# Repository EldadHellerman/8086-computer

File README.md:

# 8086 computer

A single board 8086 based computer with a full keyboard and RGB LCD screen.
The project includes an assembler, and maybe in the future a c compiler.

It's a new version of my 8086 computer (the old one moved to repository "8086_OLD").
This one focuses mainly on PCB design.

Folders in this repository:
 - 8086 board - KiCad project folder. Schematics and PCB design.
 - assembler - Custom 8086 assembler.
 - coprocessor - Software for the coprocessor.
 - companion - Utility to communicate with the coprocessor.

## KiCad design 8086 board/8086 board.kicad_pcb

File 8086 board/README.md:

# 8086 board
This folder is a KiCad project folder.
It includes the 8086 PC schematics and PCB design.

## Board details

### General
- The 8086 itself.
- 128/256kB SRAM + 1024kB flash with bank select switch (only 512kB are addressable at a time, so flash is divided into two banks, meaning two complete programs can be stored at once, and selected from using the switch before boot).
- Logic for address latching (including OR gate with bus ALE).
- Expansion port allowing access to 8086 bus.
This may be used for future developments - perhapse an FPGA graphics card with HDMI output.
- LED indicators for: latched adderss, memory access (SRAM 1, SRAM 2, Flash is A19, MCU, and LCD).
- Reset button.
- USB-C port for power and communication with coprocessor.

### IO
- 320*240 or 480*320 RGB 40 pin LCD.
- 32 Push Buttons.  
They form a keyboard, with 'a'-'z', space, enter, backspace, CTRL, ALT, SHIFT.
- Logic to latch data from buttons.

### Co-Processor
- Mircocontroller used to control the 8086 (generating clock and reset signals), programming the memory and generating interrupts.
- Clock source: if I dont want to generate 33% duty cycle, than maybe a lower frequency 50% duty cycle instead.
  (make 66% of 8MHz the 50% of frequency - which is 6MHz).
- Maybe also act as peripherals (with or without interrupts): timers, UART, mouse (input from touch screen), SD card interface, etc...
- USB to UART convertor (CH340C).
- USB-C port for power and to connect to computer.
- UART connector (4p header pins or JST-XH).

## Address Space

### Segments and physical address

The 8086 uses 20-bit addressing (for 1MB total).  
The physical address is calculated from a 16-bit segment register and a 16-bit address register:

```
physical address = (segment << 4) + offset
```

For convenience, I will think of each segment as being only the 4 highest order bits (0x?000), and the memory as being comprised of 16 segments, each 64kB in size.
    
For in / out instructions, only 16-bits addressing is allowed (first segment only).

The 8086 boots to address 0xFFFF0, so there must be some memory there. That's why the flash is at the top of the memory map.  
Interrupt vector table is at 0x000 - 0x100. That's why the SRAM is at the bottom of the memory map.

<details>
<summary>Tables of memory and IO maps:</summary>

### Memory map

| Addresses             | Segments  | Size  | Description                       |
| --------------------- | --------- | ----- | --------------------------------- |
| 0x0_0000 - 0x2_0000   | 0 - 1     | 128kB | SRAM                              |
| 0x2_0000 - 0x4_0000   | 2 - 3     | 128kB | optional additional SRAM          |
| 0x4_0000 - 0x6_0000   | 4 - 5     | 128kB | MMIO - Microcontroller            |
| 0x6_0000 - 0x7_0000   | 6         | 64 kB | MMIO - RGB LCD - DATA             |
| 0x7_8000 - 0x8_0000   | 7         | 64 kB | MMIO - RGB LCD  - COMMAND         |
| 0x8_0000 - 0xF_FFFF   | 8 - 15    | 512kB | Flash                             |

### IO map

IO ports are 16-bit wide.

| Number    | Address         | Read description | Write description    |
| --------- | --------------- | ---------------- | -------------------- |
| 0         | 0x0000          | 16 Push buttons. | FREE                 |
| 1         | 0x0002          | 16 Push buttons. | FREE                 |
| 2 - 7     | 0x0004 - 0x000E | FREE             | FREE                 |

</details>

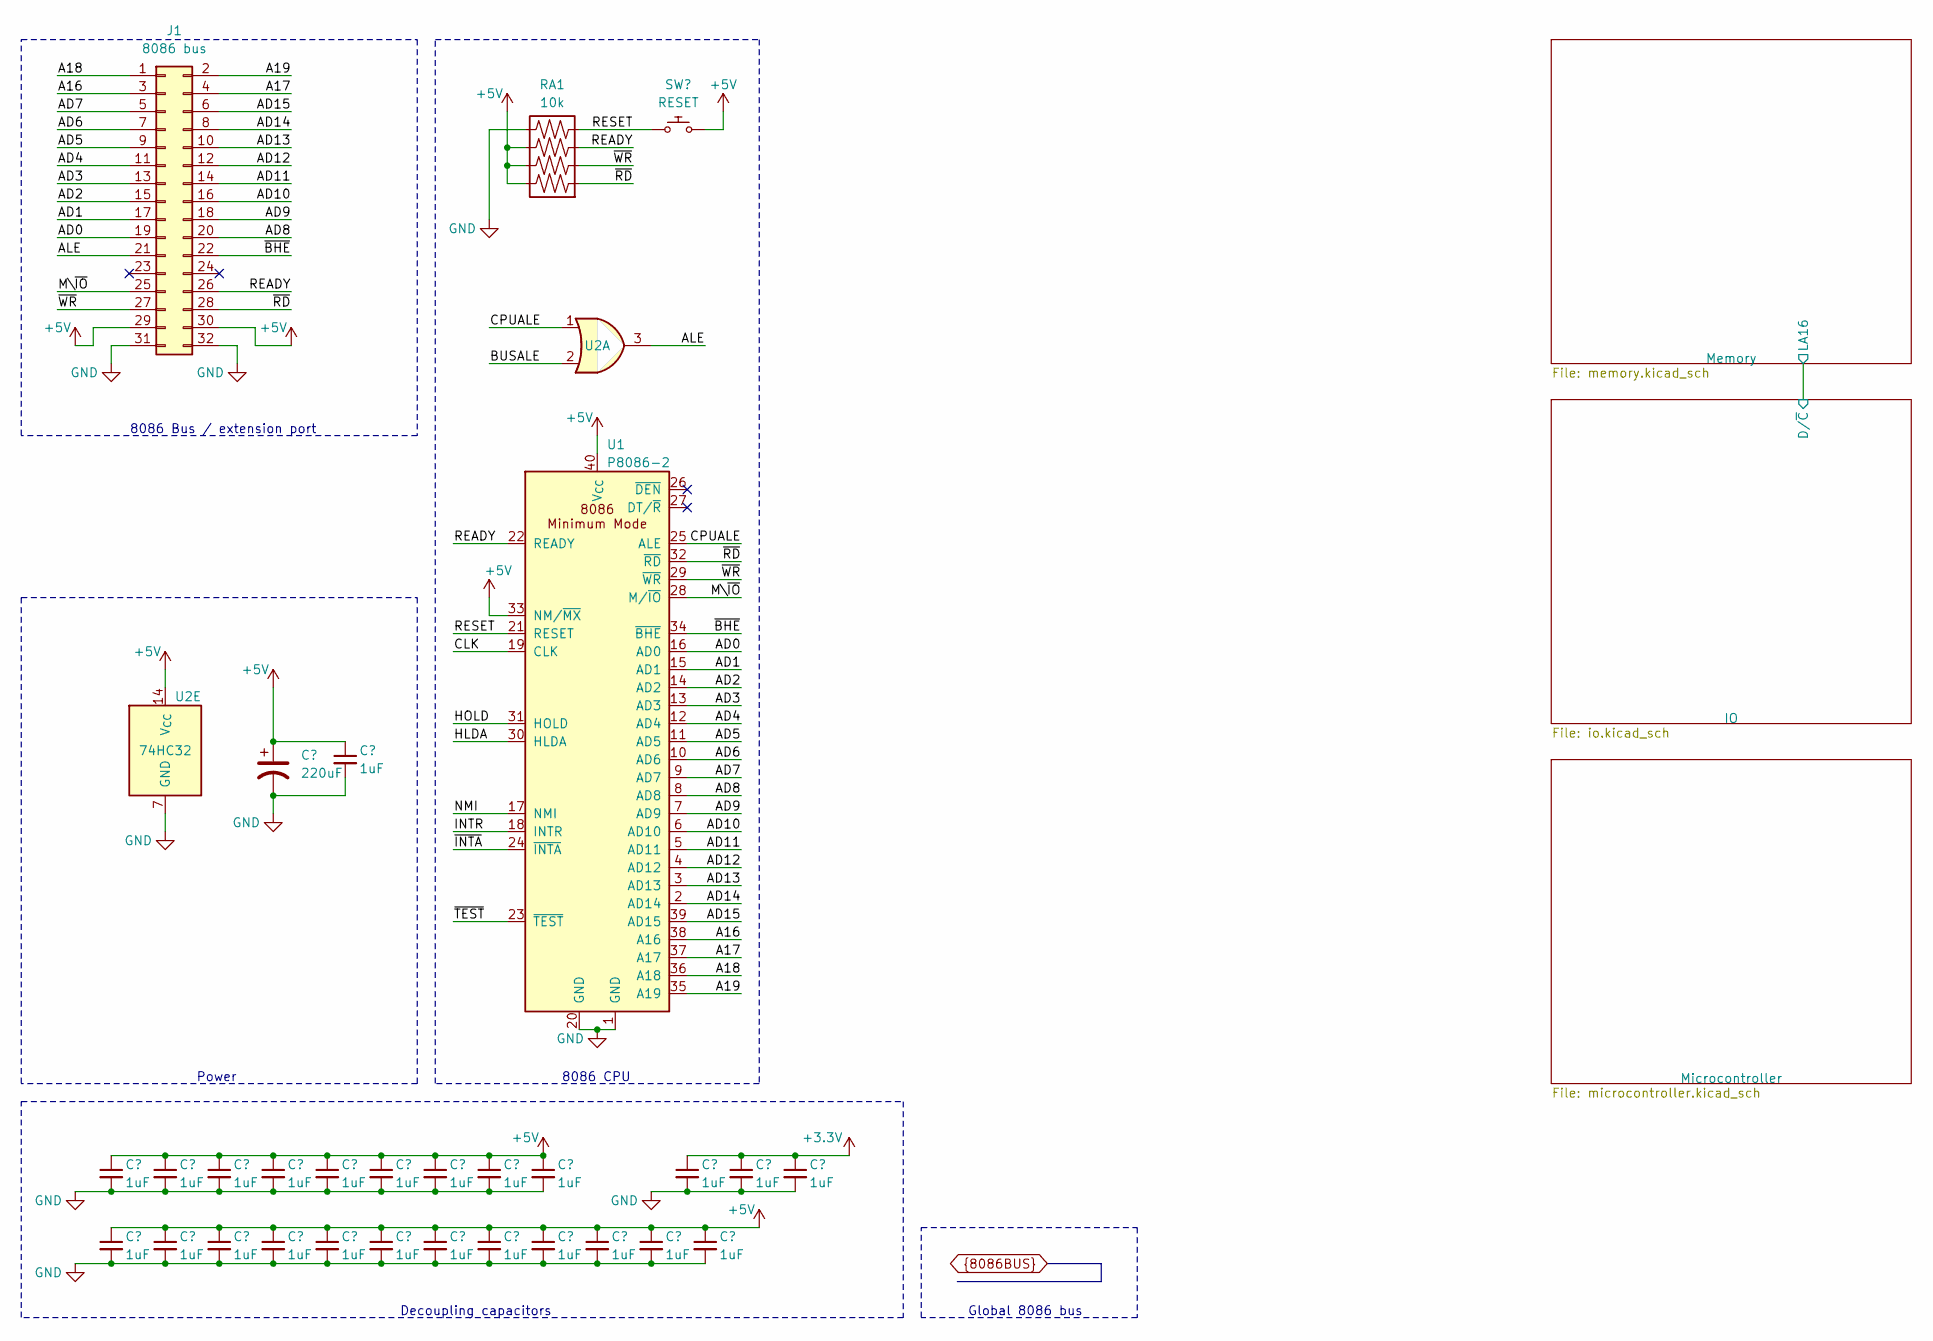
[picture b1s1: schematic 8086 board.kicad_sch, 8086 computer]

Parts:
C3: 220uF; CP_EIA-7343-43_Kemet-X_Pad2.25x2.55mm_HandSolder
C8, C9, C10, C11, C12, C13, C14, C15, C16, C17, C18, C19, C20, C21, C22, C23, C24, C25, C26, C27, C28, C29, C30, C31, C32: 1uF; C_0603_1608Metric_Pad1.08x0.95mm_HandSolder
J1: 8086 bus; PinHeader_2x16_P2.54mm_Vertical
RA1: 10k; R_Array_Concave_4x0603
SW33: RESET; SW_Push_6x6x5mm
U1: P8086-2; DIP-40_W15.24mm
U2: 74HC32; TSSOP-14_4.4x5mm_P0.65mm

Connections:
+3.3V: C17.1, C18.1, C19.1; also elsewhere on the board
+5V: C3.1, C8.1, C9.1, C10.1, C11.1, C12.1, C13.1, C14.1, C15.1, C16.1, C20.1, C21.1, C22.1, C23.1, C24.1, C25.1, C26.1, C27.1, C28.1, C29.1, C30.1, C31.1, C32.1, J1.29, J1.30, RA1.6, RA1.7, RA1.8, SW33.1, U1.33 (NM/~MX), U1.40 (V_{CC}), U2.14 (V_{CC}); also elsewhere on the board
/CPUALE: U1.25 (ALE), U2.1
A16: J1.3, U1.38 (A16); also elsewhere on the board
A17: J1.4, U1.37 (A17); also elsewhere on the board
A18: J1.1, U1.36 (A18); also elsewhere on the board
A19: J1.2, U1.35 (A19); also elsewhere on the board
AD0: J1.19, U1.16 (AD0); also elsewhere on the board
AD1: J1.17, U1.15 (AD1); also elsewhere on the board
AD2: J1.15, U1.14 (AD2); also elsewhere on the board
AD3: J1.13, U1.13 (AD3); also elsewhere on the board
AD4: J1.11, U1.12 (AD4); also elsewhere on the board
AD5: J1.9, U1.11 (AD5); also elsewhere on the board
AD6: J1.7, U1.10 (AD6); also elsewhere on the board
AD7: J1.5, U1.9 (AD7); also elsewhere on the board
AD8: J1.20, U1.8 (AD8); also elsewhere on the board
AD9: J1.18, U1.7 (AD9); also elsewhere on the board
AD10: J1.16, U1.6 (AD10); also elsewhere on the board
AD11: J1.14, U1.5 (AD11); also elsewhere on the board
AD12: J1.12, U1.4 (AD12); also elsewhere on the board
AD13: J1.10, U1.3 (AD13); also elsewhere on the board
AD14: J1.8, U1.2 (AD14); also elsewhere on the board
AD15: J1.6, U1.39 (AD15); also elsewhere on the board
ALE: J1.21, U2.3; also elsewhere on the board
BUSALE: U2.2; also elsewhere on the board
CLK: U1.19 (CLK); also elsewhere on the board
GND: C3.2, C8.2, C9.2, C10.2, C11.2, C12.2, C13.2, C14.2, C15.2, C16.2, C17.2, C18.2, C19.2, C20.2, C21.2, C22.2, C23.2, C24.2, C25.2, C26.2, C27.2, C28.2, C29.2, C30.2, C31.2, C32.2, J1.31, J1.32, RA1.5, U1.1 (GND), U1.20 (GND), U2.7 (GND); also elsewhere on the board
HLDA: U1.30 (HLDA); also elsewhere on the board
HOLD: U1.31 (HOLD); also elsewhere on the board
INTR: U1.18 (INTR); also elsewhere on the board
M\~IO: J1.25, U1.28 (M/~IO); also elsewhere on the board
NMI: U1.17 (NMI); also elsewhere on the board
READY: J1.26, RA1.3, U1.22 (READY); also elsewhere on the board
RESET: RA1.4, SW33.2, U1.21 (RESET); also elsewhere on the board
~BHE: J1.22, U1.34 (~BHE); also elsewhere on the board
~INTA: U1.24 (~INTA); also elsewhere on the board
~RD: J1.28, RA1.1, U1.32 (~RD); also elsewhere on the board
~TEST: U1.23 (~TEST); also elsewhere on the board
~WR: J1.27, RA1.2, U1.29 (~WR); also elsewhere on the board

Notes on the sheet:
Power
8086 Bus / extension port
Decoupling capacitors
Global 8086 bus
8086 CPU

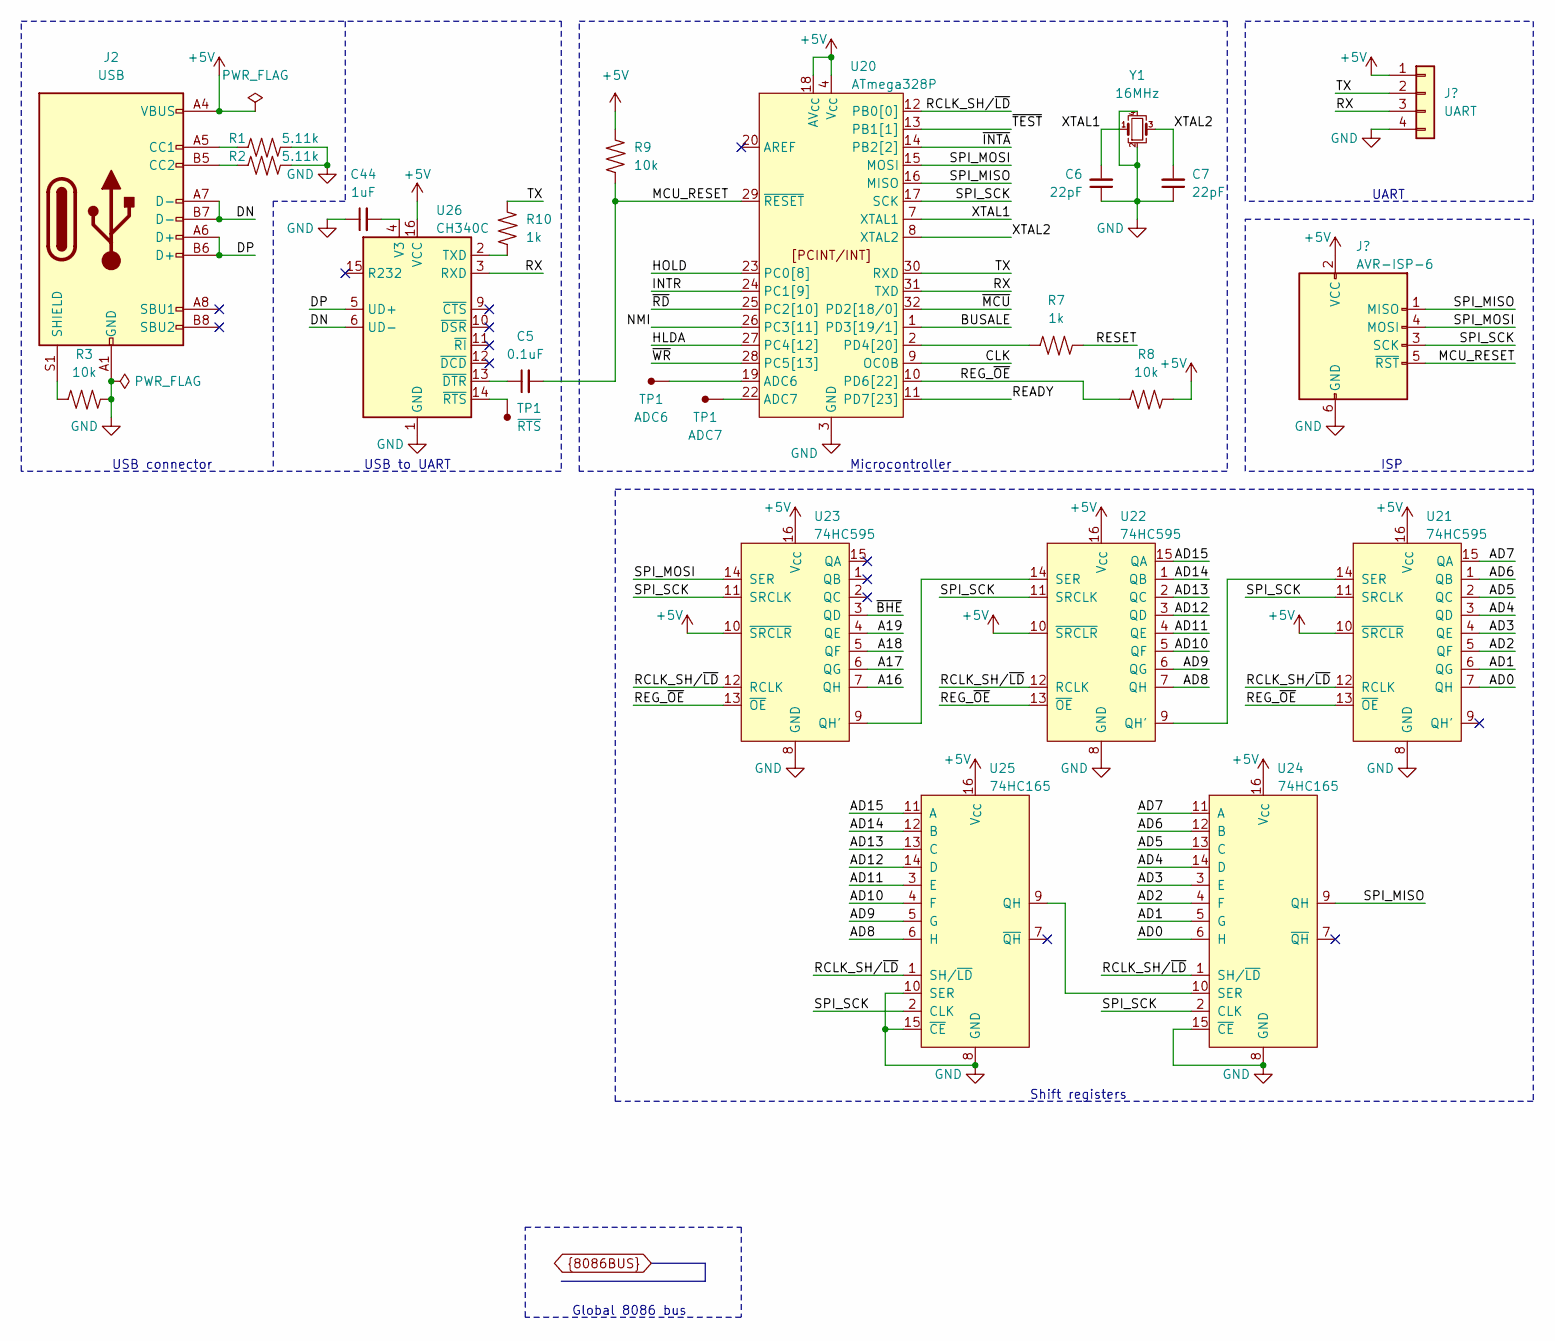
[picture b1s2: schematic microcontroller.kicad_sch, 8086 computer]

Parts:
C5: 0.1uF; C_0603_1608Metric_Pad1.08x0.95mm_HandSolder
C6, C7: 22pF; C_0603_1608Metric_Pad1.08x0.95mm_HandSolder
C44: 1uF; C_0603_1608Metric_Pad1.08x0.95mm_HandSolder
J2: USB; USB_C_Receptacle_GCT_USB4105-xx-A_16P_TopMnt_Horizontal
J4: UART; PinHeader_1x04_P2.54mm_Vertical
J5: AVR-ISP-6; PinHeader_2x03_P2.54mm_Vertical
R1, R2: 5.11k; R_0603_1608Metric_Pad0.98x0.95mm_HandSolder
R3, R8, R9: 10k; R_0603_1608Metric_Pad0.98x0.95mm_HandSolder
R7, R10: 1k; R_0603_1608Metric_Pad0.98x0.95mm_HandSolder
TP1: ADC6; TestPoint_Pad_1.5x1.5mm
U20: ATmega328P; TQFP-32_7x7mm_P0.8mm
U21, U22, U23: 74HC595; TSSOP-16_4.4x5mm_P0.65mm
U24, U25: 74HC165; TSSOP-16_4.4x5mm_P0.65mm
U26: CH340C; SOIC-16_3.9x9.9mm_P1.27mm
Y1: 16MHz; Crystal_SMD_3225-4Pin_3.2x2.5mm_HandSoldering

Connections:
+5V: J2.A4 (VBUS), J2.A9 (VBUS), J2.B4 (VBUS), J2.B9 (VBUS), J4.1, J5.2 (VCC), R8.2, R9.2, U20.4 (V_{CC}), U20.6 (V_{CC}), U20.18 (AV_{CC}), U21.10 (~SRCLR), U21.16 (V_{CC}), U22.10 (~SRCLR), U22.16 (V_{CC}), U23.10 (~SRCLR), U23.16 (V_{CC}), U24.16 (V_{CC}), U25.16 (V_{CC}); also elsewhere on the board
/Microcontroller/DN: J2.A7 (D-), J2.B7 (D-); also elsewhere on the board
/Microcontroller/DP: J2.A6 (D+), J2.B6 (D+); also elsewhere on the board
/Microcontroller/MCU_RESET: C5.2, J5.5 (~RST), R9.1, U20.29 (~RESET)
/Microcontroller/RCLK_SH/~LD: U20.12 (PB0[0]), U21.12 (RCLK), U22.12 (RCLK), U23.12 (RCLK), U24.1 (SH/~LD), U25.1 (SH/~LD)
/Microcontroller/REG_~OE: R8.1, U20.10 (PD6[22]), U21.13 (~OE), U22.13 (~OE), U23.13 (~OE)
/Microcontroller/RX: J4.3, U20.31 (TXD); also elsewhere on the board
/Microcontroller/SPI_MISO: J5.1 (MISO), U20.16 (MISO), U24.9 (QH)
/Microcontroller/SPI_MOSI: J5.4 (MOSI), U20.15 (MOSI), U23.14 (SER)
/Microcontroller/SPI_SCK: J5.3 (SCK), U20.17 (SCK), U21.11 (SRCLK), U22.11 (SRCLK), U23.11 (SRCLK), U24.2 (CLK), U25.2 (CLK)
/Microcontroller/TX: J4.2, R10.2, U20.30 (RXD)
/Microcontroller/XTAL1: C6.2, U20.7 (XTAL1), Y1.1
/Microcontroller/XTAL2: C7.2, U20.8 (XTAL2), Y1.3
A16: U23.7 (QH); also elsewhere on the board
A17: U23.6 (QG); also elsewhere on the board
A18: U23.5 (QF); also elsewhere on the board
A19: U23.4 (QE); also elsewhere on the board
AD0: U21.7 (QH), U24.6 (H); also elsewhere on the board
AD1: U21.6 (QG), U24.5 (G); also elsewhere on the board
AD2: U21.5 (QF), U24.4 (F); also elsewhere on the board
AD3: U21.4 (QE), U24.3 (E); also elsewhere on the board
AD4: U21.3 (QD), U24.14 (D); also elsewhere on the board
AD5: U21.2 (QC), U24.13 (C); also elsewhere on the board
AD6: U21.1 (QB), U24.12 (B); also elsewhere on the board
AD7: U21.15 (QA), U24.11 (A); also elsewhere on the board
AD8: U22.7 (QH), U25.6 (H); also elsewhere on the board
AD9: U22.6 (QG), U25.5 (G); also elsewhere on the board
AD10: U22.5 (QF), U25.4 (F); also elsewhere on the board
AD11: U22.4 (QE), U25.3 (E); also elsewhere on the board
AD12: U22.3 (QD), U25.14 (D); also elsewhere on the board
AD13: U22.2 (QC), U25.13 (C); also elsewhere on the board
AD14: U22.1 (QB), U25.12 (B); also elsewhere on the board
AD15: U22.15 (QA), U25.11 (A); also elsewhere on the board
BUSALE: U20.1 (PD3[19/1]); also elsewhere on the board
CLK: U20.9 (OC0B); also elsewhere on the board
GND: C6.1, C7.1, J2.A1 (GND), J2.A12 (GND), J2.B1 (GND), J2.B12 (GND), J4.4, J5.6 (GND), R1.2, R2.2, R3.2, U20.3 (GND), U20.5 (GND), U20.21 (GND), U21.8 (GND), U22.8 (GND), U23.8 (GND), U24.8 (GND), U24.15 (~CE), U25.8 (GND), U25.10 (SER), U25.15 (~CE), Y1.2, Y1.4; also elsewhere on the board
HLDA: U20.27 (PC4[12]); also elsewhere on the board
HOLD: U20.23 (PC0[8]); also elsewhere on the board
INTR: U20.24 (PC1[9]); also elsewhere on the board
NMI: U20.26 (PC3[11]); also elsewhere on the board
unnamed: J2.A5 (CC1), R1.1
unnamed: J2.B5 (CC2), R2.1
unnamed: J2.S1 (SHIELD), R3.1
unnamed 155: R10.1; also elsewhere on the board
unnamed 157: C5.1; also elsewhere on the board
unnamed: R7.1, U20.2 (PD4[20])
unnamed: U21.14 (SER), U22.9 (QH')
unnamed: U22.14 (SER), U23.9 (QH')
unnamed: U24.10 (SER), U25.9 (QH)
READY: U20.11 (PD7[23]); also elsewhere on the board
RESET: R7.2; also elsewhere on the board
~BHE: U23.3 (QD); also elsewhere on the board
~INTA: U20.14 (PB2[2]); also elsewhere on the board
~MCU: U20.32 (PD2[18/0]); also elsewhere on the board
~RD: U20.25 (PC2[10]); also elsewhere on the board
~TEST: U20.13 (PB1[1]); also elsewhere on the board
~WR: U20.28 (PC5[13]); also elsewhere on the board

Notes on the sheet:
UART
ISP
Microcontroller
USB to UART
USB connector
Global 8086 bus
Shift registers

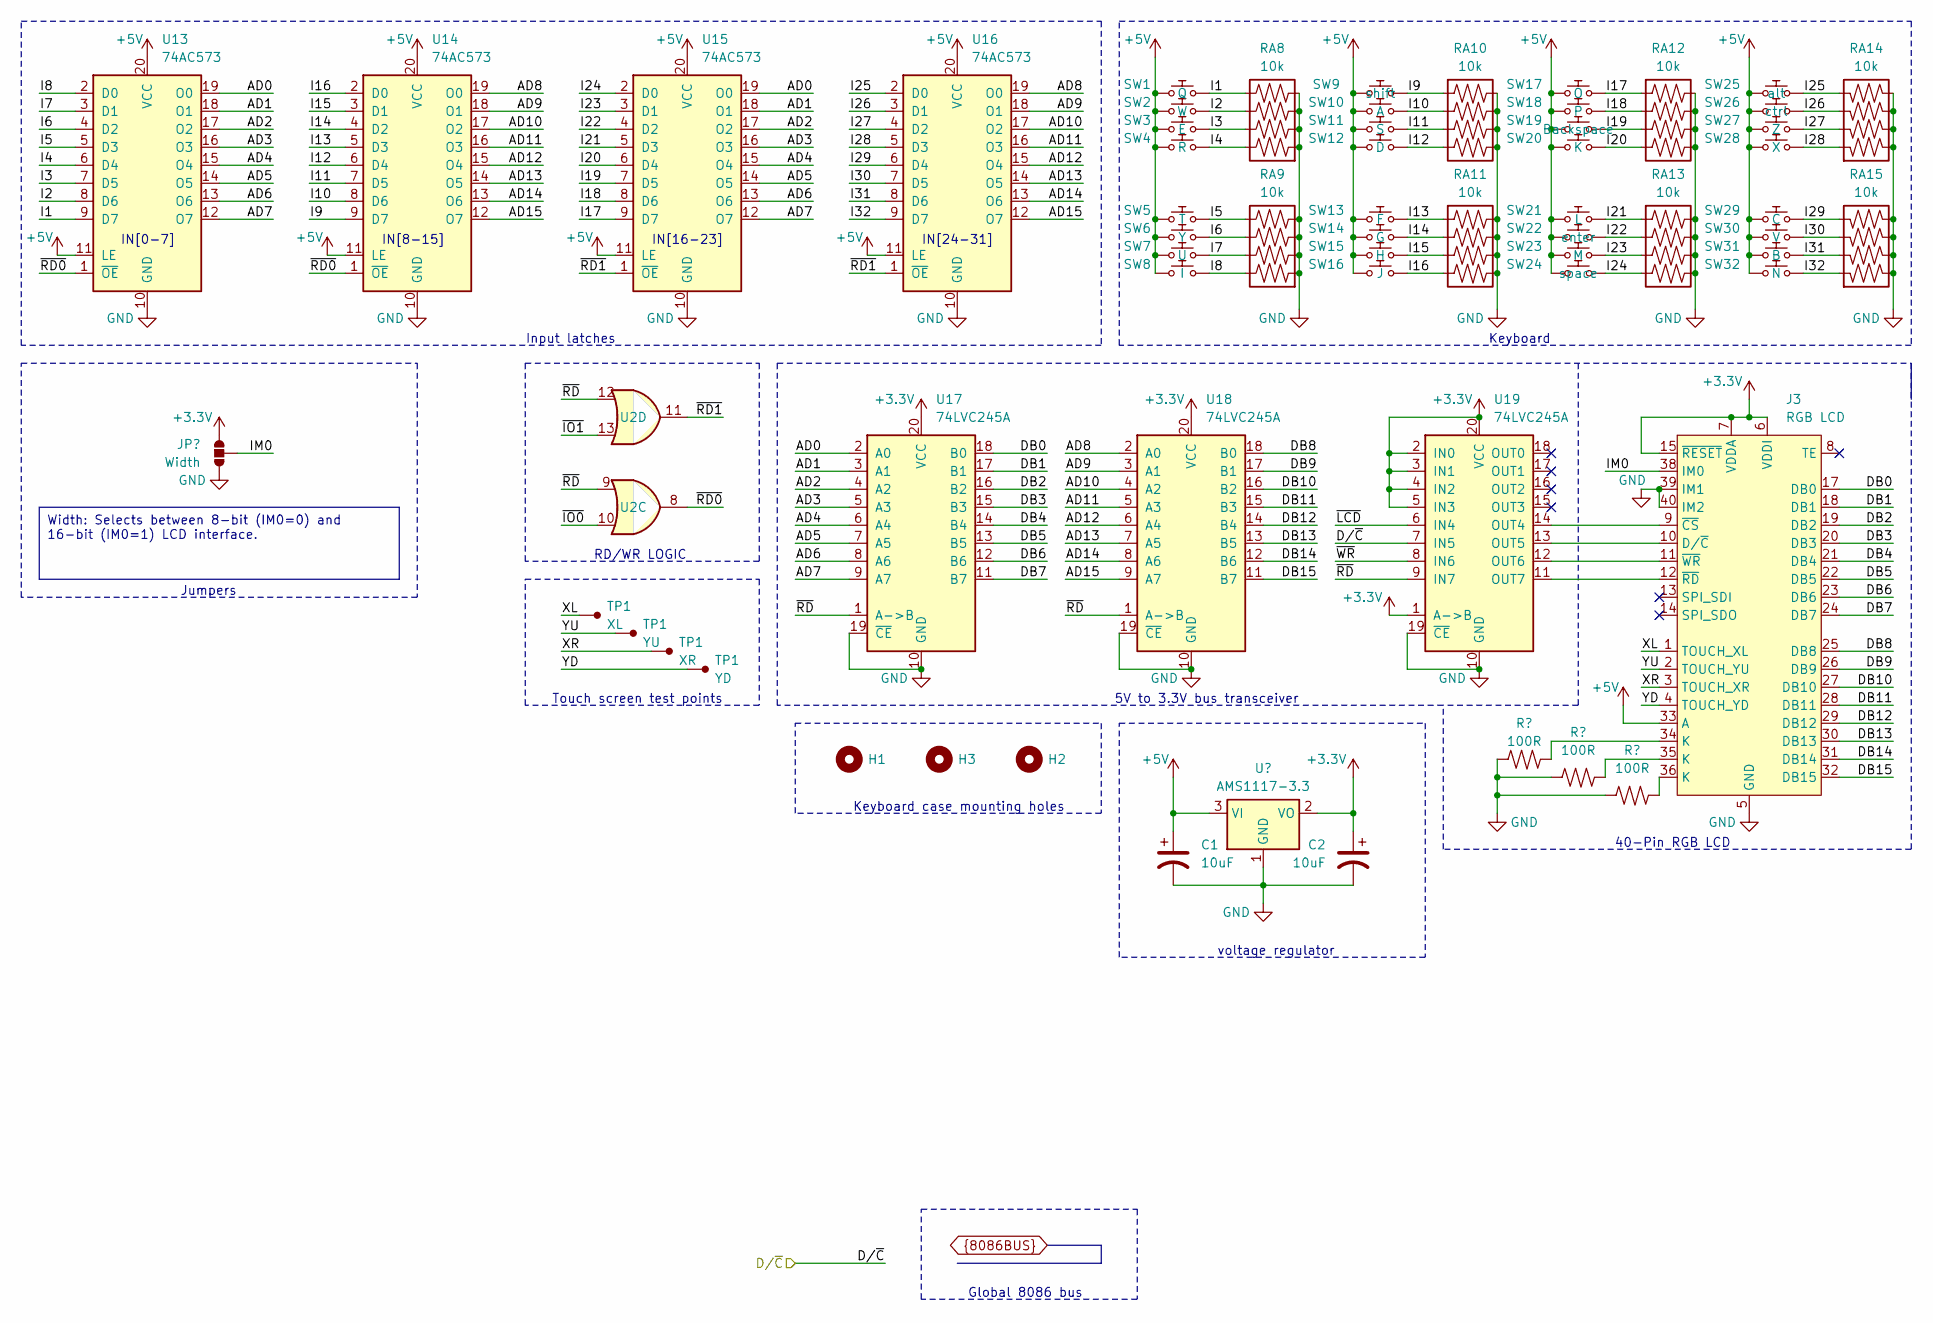
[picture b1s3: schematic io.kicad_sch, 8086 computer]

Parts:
C1, C2: 10uF; C_0603_1608Metric_Pad1.08x0.95mm_HandSolder
H1, H2, H3: MountingHole_3.2mm_M3_DIN965
J3: RGB LCD; FPC_40
JP1: Width; SolderJumper-3_P1.3mm_Bridged12_RoundedPad1.0x1.5mm
R4, R5, R6: 100R; R_0603_1608Metric_Pad0.98x0.95mm_HandSolder
RA8, RA9, RA10, RA11, RA12, RA13, RA14, RA15: 10k; R_Array_Concave_4x0603
SW1: Q; SW_Push_6x6x5mm
SW2: W; SW_Push_6x6x5mm
SW3: E; SW_Push_6x6x5mm
SW4: R; SW_Push_6x6x5mm
SW5: T; SW_Push_6x6x5mm
SW6: Y; SW_Push_6x6x5mm
SW7: U; SW_Push_6x6x5mm
SW8: I; SW_Push_6x6x5mm
SW9: shift; SW_Push_6x6x5mm
SW10: A; SW_Push_6x6x5mm
SW11: S; SW_Push_6x6x5mm
SW12: D; SW_Push_6x6x5mm
SW13: F; SW_Push_6x6x5mm
SW14: G; SW_Push_6x6x5mm
SW15: H; SW_Push_6x6x5mm
SW16: J; SW_Push_6x6x5mm
SW17: O; SW_Push_6x6x5mm
SW18: P; SW_Push_6x6x5mm
SW19: Backspace; SW_Push_6x6x5mm
SW20: K; SW_Push_6x6x5mm
SW21: L; SW_Push_6x6x5mm
SW22: enter; SW_Push_6x6x5mm
SW23: M; SW_Push_6x6x5mm
SW24: space; SW_Push_6x6x5mm
SW25: alt; SW_Push_6x6x5mm
SW26: ctrl; SW_Push_6x6x5mm
SW27: Z; SW_Push_6x6x5mm
SW28: X; SW_Push_6x6x5mm
SW29: C; SW_Push_6x6x5mm
SW30: V; SW_Push_6x6x5mm
SW31: B; SW_Push_6x6x5mm
SW32: N; SW_Push_6x6x5mm
TP1: XR; TestPoint_Pad_1.5x1.5mm
U2: 74HC32; TSSOP-14_4.4x5mm_P0.65mm
U3: AMS1117-3.3; SOT-223-3_TabPin2
U13, U14, U15, U16: 74AC573; TSSOP-20_4.4x6.5mm_P0.65mm
U17, U18, U19: 74LVC245A; TSSOP-20_4.4x6.5mm_P0.65mm

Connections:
+3.3V: C2.1, J3.6 (VDDI), J3.7 (VDDA), J3.15 (~RESET), JP1.1, U3.2 (VO), U17.20 (VCC), U18.20 (VCC), U19.1 (A->B), U19.2 (IN0), U19.3 (IN1), U19.4 (IN2), U19.5 (IN3), U19.20 (VCC); also elsewhere on the board
+5V: C1.1, J3.33 (A), SW1.1, SW2.2, SW3.1, SW4.2, SW5.1, SW6.2, SW7.1, SW8.2, SW9.1, SW10.2, SW11.1, SW12.2, SW13.1, SW14.2, SW15.1, SW16.2, SW17.1, SW18.2, SW19.1, SW20.1, SW21.2, SW22.1, SW23.1, SW24.1, SW25.1, SW26.2, SW27.1, SW28.2, SW29.1, SW30.2, SW31.1, SW32.2, U3.3 (VI), U13.11 (LE), U13.20 (VCC), U14.11 (LE), U14.20 (VCC), U15.11 (LE), U15.20 (VCC), U16.11 (LE), U16.20 (VCC); also elsewhere on the board
/IO/DB0: J3.17 (DB0), U17.18 (B0)
/IO/DB1: J3.18 (DB1), U17.17 (B1)
/IO/DB2: J3.19 (DB2), U17.16 (B2)
/IO/DB3: J3.20 (DB3), U17.15 (B3)
/IO/DB4: J3.21 (DB4), U17.14 (B4)
/IO/DB5: J3.22 (DB5), U17.13 (B5)
/IO/DB6: J3.23 (DB6), U17.12 (B6)
/IO/DB7: J3.24 (DB7), U17.11 (B7)
/IO/DB8: J3.25 (DB8), U18.18 (B0)
/IO/DB9: J3.26 (DB9), U18.17 (B1)
/IO/DB10: J3.27 (DB10), U18.16 (B2)
/IO/DB11: J3.28 (DB11), U18.15 (B3)
/IO/DB12: J3.29 (DB12), U18.14 (B4)
/IO/DB13: J3.30 (DB13), U18.13 (B5)
/IO/DB14: J3.31 (DB14), U18.12 (B6)
/IO/DB15: J3.32 (DB15), U18.11 (B7)
/IO/D/~C: U19.7 (IN5); also elsewhere on the board
/IO/I1: RA8.5, SW1.2, U13.9 (D7)
/IO/I2: RA8.6, SW2.1, U13.8 (D6)
/IO/I3: RA8.7, SW3.2, U13.7 (D5)
/IO/I4: RA8.8, SW4.1, U13.6 (D4)
/IO/I5: RA9.5, SW5.2, U13.5 (D3)
/IO/I6: RA9.6, SW6.1, U13.4 (D2)
/IO/I7: RA9.7, SW7.2, U13.3 (D1)
/IO/I8: RA9.8, SW8.1, U13.2 (D0)
/IO/I9: RA10.1, SW9.2, U14.9 (D7)
/IO/I10: RA10.2, SW10.1, U14.8 (D6)
/IO/I11: RA10.3, SW11.2, U14.7 (D5)
/IO/I12: RA10.4, SW12.1, U14.6 (D4)
/IO/I13: RA11.1, SW13.2, U14.5 (D3)
/IO/I14: RA11.2, SW14.1, U14.4 (D2)
/IO/I15: RA11.3, SW15.2, U14.3 (D1)
/IO/I16: RA11.4, SW16.1, U14.2 (D0)
/IO/I17: RA12.1, SW17.2, U15.9 (D7)
/IO/I18: RA12.2, SW18.1, U15.8 (D6)
/IO/I19: RA12.3, SW19.2, U15.7 (D5)
/IO/I20: RA12.4, SW20.2, U15.6 (D4)
/IO/I21: RA13.1, SW21.1, U15.5 (D3)
/IO/I22: RA13.2, SW22.2, U15.4 (D2)
/IO/I23: RA13.3, SW23.2, U15.3 (D1)
/IO/I24: RA13.4, SW24.2, U15.2 (D0)
/IO/I25: RA14.4, SW25.2, U16.2 (D0)
/IO/I26: RA14.3, SW26.1, U16.3 (D1)
/IO/I27: RA14.2, SW27.2, U16.4 (D2)
/IO/I28: RA14.1, SW28.1, U16.5 (D3)
/IO/I29: RA15.4, SW29.2, U16.6 (D4)
/IO/I30: RA15.3, SW30.1, U16.7 (D5)
/IO/I31: RA15.2, SW31.2, U16.8 (D6)
/IO/I32: RA15.1, SW32.1, U16.9 (D7)
/IO/IM0: J3.38 (IM0), JP1.2
/IO/~RD0: U2.8, U13.1 (~OE), U14.1 (~OE)
/IO/~RD1: U2.11, U15.1 (~OE), U16.1 (~OE)
AD0: U13.19 (O0), U15.19 (O0), U17.2 (A0); also elsewhere on the board
AD1: U13.18 (O1), U15.18 (O1), U17.3 (A1); also elsewhere on the board
AD2: U13.17 (O2), U15.17 (O2), U17.4 (A2); also elsewhere on the board
AD3: U13.16 (O3), U15.16 (O3), U17.5 (A3); also elsewhere on the board
AD4: U13.15 (O4), U15.15 (O4), U17.6 (A4); also elsewhere on the board
AD5: U13.14 (O5), U15.14 (O5), U17.7 (A5); also elsewhere on the board
AD6: U13.13 (O6), U15.13 (O6), U17.8 (A6); also elsewhere on the board
AD7: U13.12 (O7), U15.12 (O7), U17.9 (A7); also elsewhere on the board
AD8: U14.19 (O0), U16.19 (O0), U18.2 (A0); also elsewhere on the board
AD9: U14.18 (O1), U16.18 (O1), U18.3 (A1); also elsewhere on the board
AD10: U14.17 (O2), U16.17 (O2), U18.4 (A2); also elsewhere on the board
AD11: U14.16 (O3), U16.16 (O3), U18.5 (A3); also elsewhere on the board
AD12: U14.15 (O4), U16.15 (O4), U18.6 (A4); also elsewhere on the board
AD13: U14.14 (O5), U16.14 (O5), U18.7 (A5); also elsewhere on the board
AD14: U14.13 (O6), U16.13 (O6), U18.8 (A6); also elsewhere on the board
AD15: U14.12 (O7), U16.12 (O7), U18.9 (A7); also elsewhere on the board
GND: C1.2, C2.2, J3.5 (GND), J3.16 (GND), J3.37 (GND), J3.39 (IM1), J3.40 (IM2), JP1.3, R4.1, R5.1, R6.1, RA8.1, RA8.2, RA8.3, RA8.4, RA9.1, RA9.2, RA9.3, RA9.4, RA10.5, RA10.6, RA10.7, RA10.8, RA11.5, RA11.6, RA11.7, RA11.8, RA12.5, RA12.6, RA12.7, RA12.8, RA13.5, RA13.6, RA13.7, RA13.8, RA14.5, RA14.6, RA14.7, RA14.8, RA15.5, RA15.6, RA15.7, RA15.8, U3.1 (GND), U13.10 (GND), U14.10 (GND), U15.10 (GND), U16.10 (GND), U17.10 (GND), U17.19 (~CE), U18.10 (GND), U18.19 (~CE), U19.10 (GND), U19.19 (~CE); also elsewhere on the board
unnamed: J3.10 (D/~C), U19.13 (OUT5)
unnamed: J3.34 (K), R4.2
unnamed: J3.35 (K), R5.2
unnamed: J3.36 (K), R6.2
unnamed: J3.9 (~CS), U19.14 (OUT4)
unnamed: J3.12 (~RD), U19.11 (OUT7)
unnamed: J3.11 (~WR), U19.12 (OUT6)
~IO0: U2.10; also elsewhere on the board
~IO1: U2.13; also elsewhere on the board
~LCD: U19.6 (IN4); also elsewhere on the board
~RD: U2.9, U2.12, U17.1 (A->B), U18.1 (A->B), U19.9 (IN7); also elsewhere on the board
~WR: U19.8 (IN6); also elsewhere on the board

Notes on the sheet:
Width: Selects between 8-bit (IM0=0) and 16-bit (IM0=1) LCD interface.
5V to 3.3V bus transceiver
Global 8086 bus
Touch screen test points
voltage regulator
Keyboard
IN[16-23]
IN[24-31]
Input latches
Keyboard case mounting holes
IN[8-15]
IN[0-7]
RD/WR LOGIC
Jumpers
40-Pin RGB LCD

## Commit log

2023-08-29 init
2023-08-29 added modules description
2023-08-29 first test of schmatic bus and PCB concept
2023-08-29 8086 module - bus connected
2023-08-30 8086 module - address latches, start of memory ICs
2023-08-30 IO addresses changed to accomedate 16-bit wide IO
2023-08-30 - changed SEG and IO pins to bidirectional - added "Local to Module" netclass.
2023-09-10 change IO module to full keyboard
2023-09-10 split 8086 module to two files
2023-09-10 basic start for microcontroller module
2023-09-10 basic start for IO module
2023-09-13 initial PCB layout with almost accurate footprints
2023-09-13 move to single board design
2023-09-14 refactoring schematic files and structure
2023-09-24 better schematic. initial pcb layout
2023-09-27 adds assembler mnemonics
2023-09-27 .gitignore file per subfolder
2023-09-29 adds instruction first byte format fields
2023-10-01 - adds instruction format struct - removes 'z' instruction format field - changed mnemonics table - adds mnemonic synonym table
2023-10-01 preprocessor init
2023-10-01 test.c init
2023-10-01 refactoring: adds main.c
2023-10-01 tokenizer init
2023-10-01 adds local .gitignore file
2023-10-01 - all instructions encoded - improved instruction format encoding - improved instruction printing method
2023-10-01 removes synonyms table
    On a 16-bit system, the memory consumption is the same,
    and on a computer, it's irrelevant anyway
    This also makes programming easier and execution faster.
2023-10-01 refactoring: better IF_IMPLICIT_DX names
2023-10-01 change instruction suffix from flags to numbers.
2023-10-01 order instructions with multiple formats by priority
2023-10-15 - move preprocessor to assembler folder. - assembly syntax, directives, and preprocessor directives. - better makefile
2023-10-15 - move board readme to "8086 board" folder - create project readme file
2023-10-15 refactoring: rename "test" to "tests"
2023-10-15 refactor "assembly syntax.md" to assembler README
2023-10-15 add test programs
2023-10-15 add directives strings
2023-10-15 - add directives strings to isa - change isa registers to string only
2023-10-15 - add preprocessor directives strings
2023-10-15 add preprocessor directive "#if"
2023-10-15 add working basic tokenizer
2023-10-15 add lunch configuration for debugging
2023-10-16 - add escaped char consts - printing from print.h (with colors)
2023-10-17 add more tests generation
2023-10-17 add tokenizer suppor for escaped character
2023-10-25 Schematic finished! (some footprint assignments are still needed)
2023-10-26 add drawing sheet template
2023-10-26 -remove power switch -add testpoints for unused logic gate
2023-10-26 -add LCD bus transceiver -add jumper for 7 segments common pin to ground or vcc
2023-10-26 change to 4 pin crystal
2023-10-27 change readme
2023-10-27 change 7 segment to custom symbol and footprint
2023-10-27 initial pcb
2023-10-27 move assembling to assembler.c
2023-10-28 change to alternate pins of atmega328p
2023-10-28 change 74HC373D (SO20) to 74HC573PW (TSSOP20)
2023-10-29 change schematic to use new components
2023-10-29 start memory layout
2023-10-29 connect flash and ram together
2023-10-30 reduced schematic, PCB memory routed
2023-11-01 schematic: reduced 8086 bus, no LCD shield
2023-11-01 PCB: initial layout
2023-11-03 PCB: more layout work. some schematic changes.
2023-11-08 PCB: different layout
2023-11-10 PCB: layout and routing of IO, shift registers, and MCU
2023-11-15 small schematic changes to better fit PCB
2023-11-15 finish routing PCB
2023-11-15 remove LCD reset jumper
2023-11-15 finish main silkscreen
2023-11-19 schematic: fix LCD RD bug, geographical reannotation
2023-11-19 PCB: done with silkscreen
2023-11-19 PCB: V1.0.1 - add JLC text - change plot settings to fit JLC - remove unnecessary ground plane traces
2023-11-29 fix labels
2024-01-07 add clock generating functions.
2024-01-07 add gpio pin mapping and utilities
2024-01-19 add predefined clock options
2024-01-19 add uart
2024-04-26 - document uart - add uart_enable_rx_interrupt()
2024-04-26 add spi
2024-04-26 add bus
2024-04-26 add isp
2024-04-26 add main
2024-04-26 add makefile minor changes
2024-04-26 add isp protocol readme
2024-04-26 add companion
2024-04-26 PCB: move to kicad 8
2024-05-03 move companion to a seperate folder and split to files
2024-05-03 fix wrong addresses
2024-05-03 new isp protocol
2024-05-10 change isp protocol to v2.1
2024-05-10 - complete cli - refactor companion
